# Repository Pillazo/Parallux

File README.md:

The light was designed in Autodesk Fusion 360, but any STEP editor will work. The step file is zipped because the full thing is 250gb-ish

The hardware was designed in KiCad 9.0

The software is arduino IDE, I used ESP32 and Teensy for the microcontrollers

The DMX controller software, which is more sACN anyways, was written in VB.NET

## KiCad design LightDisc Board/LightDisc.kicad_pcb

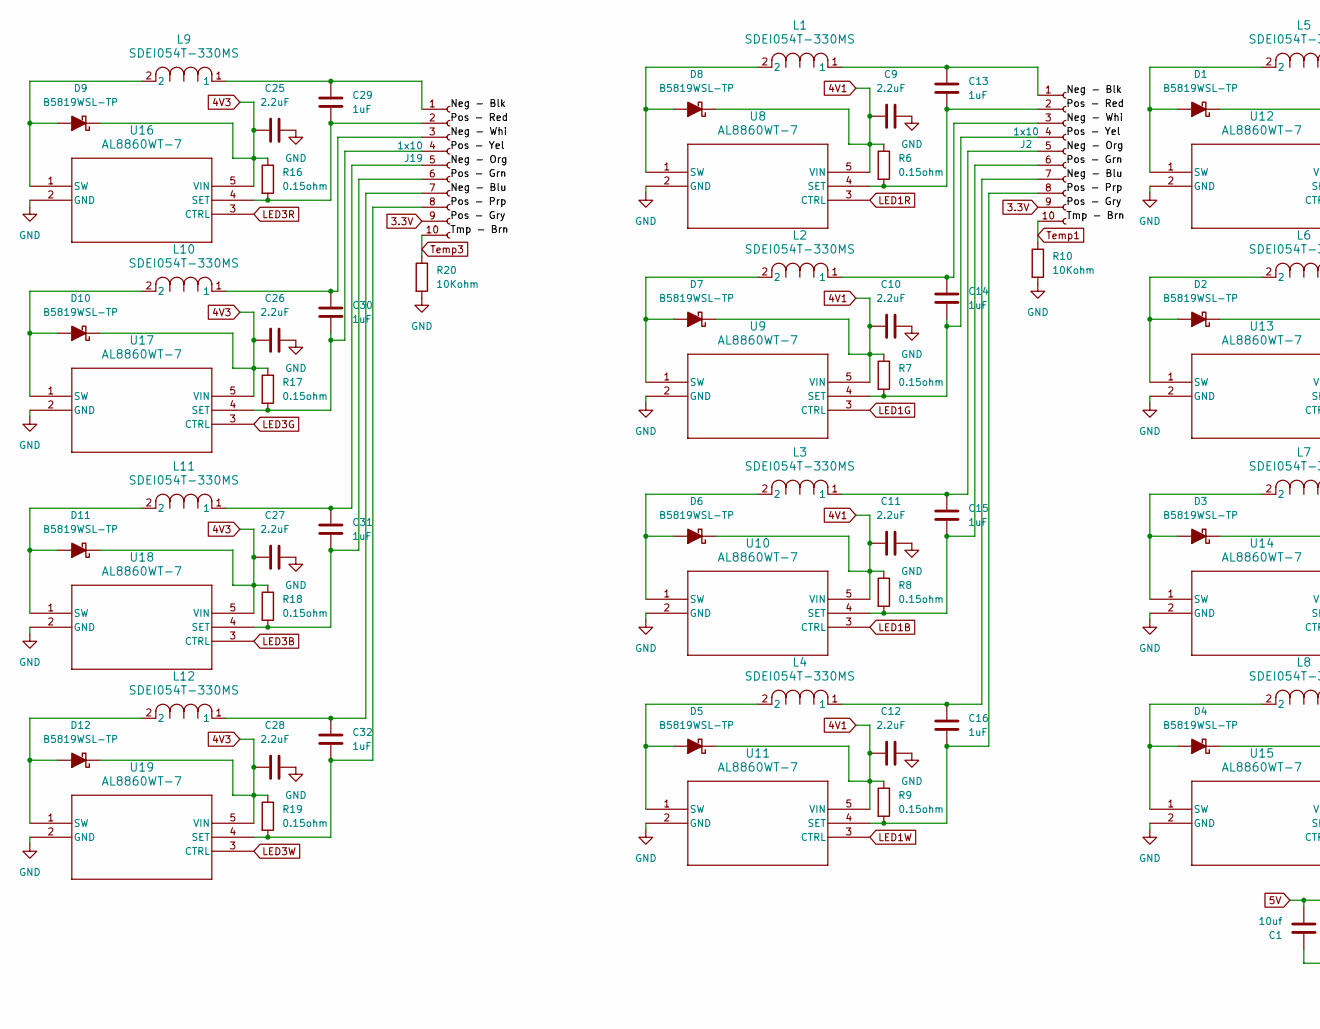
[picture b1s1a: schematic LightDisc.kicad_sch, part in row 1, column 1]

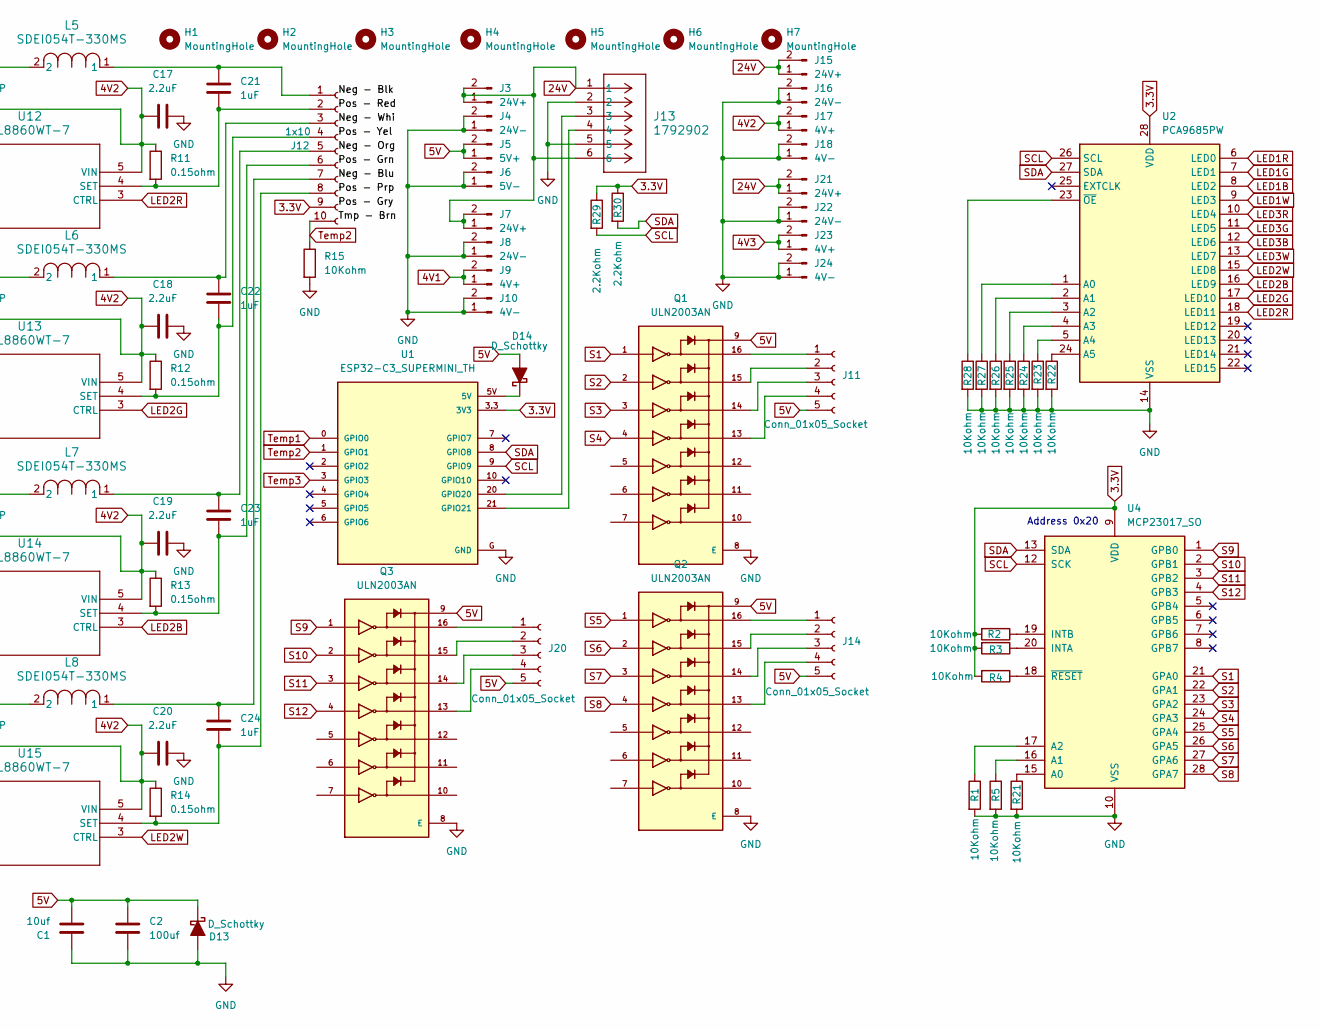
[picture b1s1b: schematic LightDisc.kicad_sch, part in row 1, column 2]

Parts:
C1: 10uf; CP_Radial_D5.0mm_P2.50mm
C2: 100uf; CP_Radial_D5.0mm_P2.50mm
C9, C10, C11, C12, C17, C18, C19, C20, C25, C26, C27, C28: 2.2uF; C_0603_1608Metric
C13, C14, C15, C16, C21, C22, C23, C24, C29, C30, C31, C32: 1uF; C_0603_1608Metric
D1, D2, D3, D4, D5, D6, D7, D8, D9, D10, D11, D12: B5819WSL-TP; D_SOD-323F
D13, D14: D_Schottky; D_SOD-323F
H1, H2, H3, H4, H5, H6, H7: MountingHole; MountingHole_3.2mm_M3
J2, J12, J19: 1x10; JST_EH_B10B-EH-A_1x10_P2.50mm_Vertical
J3, J7, J15, J21: 24V+; PinSocket_1x02_P2.54mm_Vertical
J4, J8, J16, J22: 24V-; PinSocket_1x02_P2.54mm_Vertical
J5: 5V+; PinSocket_1x02_P2.54mm_Vertical
J6: 5V-; PinSocket_1x02_P2.54mm_Vertical
J9, J17, J23: 4V+; PinSocket_1x02_P2.54mm_Vertical
J10, J18, J24: 4V-; PinSocket_1x02_P2.54mm_Vertical
J11, J14, J20: Conn_01x05_Socket; PinSocket_1x05_P2.54mm_Vertical
J13: 1792902; CONN_1792902_PXC
L1, L2, L3, L4, L5, L6, L7, L8, L9, L10, L11, L12: SDEI054T-330MS; IND_SDEI054T-330MS_CYN
Q1, Q2, Q3: ULN2003AN; CERDIP-16_W7.62mm_SideBrazed_LongPads_Socket; PARTREV P
R1, R2, R3, R4, R5, R10, R15, R20, R21, R22, R23, R24, R25, R26, R27, R28: 10Kohm; R_1206_3216Metric
R6, R7, R8, R9, R11, R12, R13, R14, R16, R17, R18, R19: 0.15ohm; R_0805_2012Metric
R29, R30: 2.2Kohm; R_1206_3216Metric
U1: ESP32-C3_SUPERMINI_TH; MODULE_ESP32-C3_SUPERMINI_TH
U2: PCA9685PW; TSSOP-28_4.4x9.7mm_P0.65mm
U4: MCP23017_SO; SOIC-28W_7.5x17.9mm_P1.27mm
U8, U9, U10, U11, U12, U13, U14, U15, U16, U17, U18, U19: AL8860WT-7; TSOT25_WT_DIO

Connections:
3.3V: J2.9, J12.9, J19.9, R2.2, R3.2, R4.2, R29.1, R30.1, U1.3.3 (3V3), U2.28 (VDD), U4.9 (VDD)
4V1: C9.2, C10.2, C11.2, C12.2, D5.1 (K), D6.1 (K), D7.1 (K), D8.1 (K), J9.1, J9.2, R6.1, R7.1, R8.1, R9.1, U8.5 (VIN), U9.5 (VIN), U10.5 (VIN), U11.5 (VIN)
4V2: C17.2, C18.2, C19.2, C20.2, D1.1 (K), D2.1 (K), D3.1 (K), D4.1 (K), J17.1, J17.2, R11.1, R12.1, R13.1, R14.1, U12.5 (VIN), U13.5 (VIN), U14.5 (VIN), U15.5 (VIN)
4V3: C25.2, C26.2, C27.2, C28.2, D9.1 (K), D10.1 (K), D11.1 (K), D12.1 (K), J23.1, J23.2, R16.1, R17.1, R18.1, R19.1, U16.5 (VIN), U17.5 (VIN), U18.5 (VIN), U19.5 (VIN)
5V: C1.2, C2.2, D13.1 (K), D14.2 (A), J5.1, J5.2, J11.5, J14.5, J20.5, Q1.9, Q2.9, Q3.9
24V: J3.1, J3.2, J7.1, J7.2, J13.1, J13.6, J15.1, J15.2, J21.1, J21.2
GND: C1.1, C2.1, C9.1, C10.1, C11.1, C12.1, C17.1, C18.1, C19.1, C20.1, C25.1, C26.1, C27.1, C28.1, D13.2 (A), J4.1, J4.2, J6.1, J6.2, J8.1, J8.2, J10.1, J10.2, J13.2, J13.5, J16.1, J16.2, J18.1, J18.2, J22.1, J22.2, J24.1, J24.2, Q1.8 (E), Q2.8 (E), Q3.8 (E), R1.2, R5.2, R10.2, R15.2, R20.2, R21.2, R22.2, R23.2, R24.2, R25.2, R26.2, R27.2, R28.2, U1.G (GND), U2.14 (VSS), U4.10 (VSS), U8.2 (GND), U9.2 (GND), U10.2 (GND), U11.2 (GND), U12.2 (GND), U13.2 (GND), U14.2 (GND), U15.2 (GND), U16.2 (GND), U17.2 (GND), U18.2 (GND), U19.2 (GND)
LED1B: U2.8 (LED2), U10.3 (CTRL)
LED1G: U2.7 (LED1), U9.3 (CTRL)
LED1R: U2.6 (LED0), U8.3 (CTRL)
LED1W: U2.9 (LED3), U11.3 (CTRL)
LED2B: U2.16 (LED9), U14.3 (CTRL)
LED2G: U2.17 (LED10), U13.3 (CTRL)
LED2R: U2.18 (LED11), U12.3 (CTRL)
LED2W: U2.15 (LED8), U15.3 (CTRL)
LED3B: U2.12 (LED6), U18.3 (CTRL)
LED3G: U2.11 (LED5), U17.3 (CTRL)
LED3R: U2.10 (LED4), U16.3 (CTRL)
LED3W: U2.13 (LED7), U19.3 (CTRL)
unnamed: D1.2 (A), L5.2, U12.1 (SW)
unnamed: D2.2 (A), L6.2, U13.1 (SW)
unnamed: D3.2 (A), L7.2, U14.1 (SW)
unnamed: D4.2 (A), L8.2, U15.1 (SW)
unnamed: D5.2 (A), L4.2, U11.1 (SW)
unnamed: D6.2 (A), L3.2, U10.1 (SW)
unnamed: D7.2 (A), L2.2, U9.1 (SW)
unnamed: D8.2 (A), L1.2, U8.1 (SW)
unnamed: D9.2 (A), L9.2, U16.1 (SW)
unnamed: D10.2 (A), L10.2, U17.1 (SW)
unnamed: D11.2 (A), L11.2, U18.1 (SW)
unnamed: D12.2 (A), L12.2, U19.1 (SW)
unnamed: D14.1 (K), U1.5V
unnamed: C13.1, J2.1, L1.1
unnamed: C13.2, J2.2, R6.2, U8.4 (SET)
unnamed: C14.1, J2.3, L2.1
unnamed: C14.2, J2.4, R7.2, U9.4 (SET)
unnamed: C15.1, J2.5, L3.1
unnamed: C15.2, J2.6, R8.2, U10.4 (SET)
unnamed: C16.1, J2.7, L4.1
unnamed: C16.2, J2.8, R9.2, U11.4 (SET)
unnamed: J11.1, Q1.16
unnamed: J11.2, Q1.15
unnamed: J11.3, Q1.14
unnamed: J11.4, Q1.13
unnamed: C21.1, J12.1, L5.1
unnamed: C21.2, J12.2, R11.2, U12.4 (SET)
unnamed: C22.1, J12.3, L6.1
unnamed: C22.2, J12.4, R12.2, U13.4 (SET)
unnamed: C23.1, J12.5, L7.1
unnamed: C23.2, J12.6, R13.2, U14.4 (SET)
unnamed: C24.1, J12.7, L8.1
unnamed: C24.2, J12.8, R14.2, U15.4 (SET)
unnamed: J14.1, Q2.16
unnamed: J14.2, Q2.15
unnamed: J14.3, Q2.14
unnamed: J14.4, Q2.13
unnamed: C29.1, J19.1, L9.1
unnamed: C29.2, J19.2, R16.2, U16.4 (SET)
unnamed: C30.1, J19.3, L10.1
unnamed: C30.2, J19.4, R17.2, U17.4 (SET)
unnamed: C31.1, J19.5, L11.1
unnamed: C31.2, J19.6, R18.2, U18.4 (SET)
unnamed: C32.1, J19.7, L12.1
unnamed: C32.2, J19.8, R19.2, U19.4 (SET)
unnamed: J20.1, Q3.16
unnamed: J20.2, Q3.15
unnamed: J20.3, Q3.14
unnamed: J20.4, Q3.13
unnamed: J13.3, U1.20 (GPIO20)
unnamed: J13.4, U1.21 (GPIO21)
unnamed: R27.1, U2.1 (A0)
unnamed: R26.1, U2.2 (A1)
unnamed: R25.1, U2.3 (A2)
unnamed: R24.1, U2.4 (A3)
unnamed: R23.1, U2.5 (A4)
unnamed: R22.1, U2.24 (A5)
unnamed: R28.1, U2.23 (~OE)
unnamed: R21.1, U4.15 (A0)
unnamed: R5.1, U4.16 (A1)
unnamed: R1.1, U4.17 (A2)
unnamed: R3.1, U4.20 (INTA)
unnamed: R2.1, U4.19 (INTB)
unnamed: R4.1, U4.18 (~RESET)
S1: Q1.1, U4.21 (GPA0)
S2: Q1.2, U4.22 (GPA1)
S3: Q1.3, U4.23 (GPA2)
S4: Q1.4, U4.24 (GPA3)
S5: Q2.1, U4.25 (GPA4)
S6: Q2.2, U4.26 (GPA5)
S7: Q2.3, U4.27 (GPA6)
S8: Q2.4, U4.28 (GPA7)
S9: Q3.1, U4.1 (GPB0)
S10: Q3.2, U4.2 (GPB1)
S11: Q3.3, U4.3 (GPB2)
S12: Q3.4, U4.4 (GPB3)
SCL: R29.2, U1.9 (GPIO9), U2.26 (SCL), U4.12 (SCK)
SDA: R30.2, U1.8 (GPIO8), U2.27 (SDA), U4.13 (SDA)
Temp1: J2.10, R10.1, U1.0 (GPIO0)
Temp2: J12.10, R15.1, U1.1 (GPIO1)
Temp3: J19.10, R20.1, U1.2 (GPIO2), U1.3 (GPIO3)

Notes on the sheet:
Address 0x20

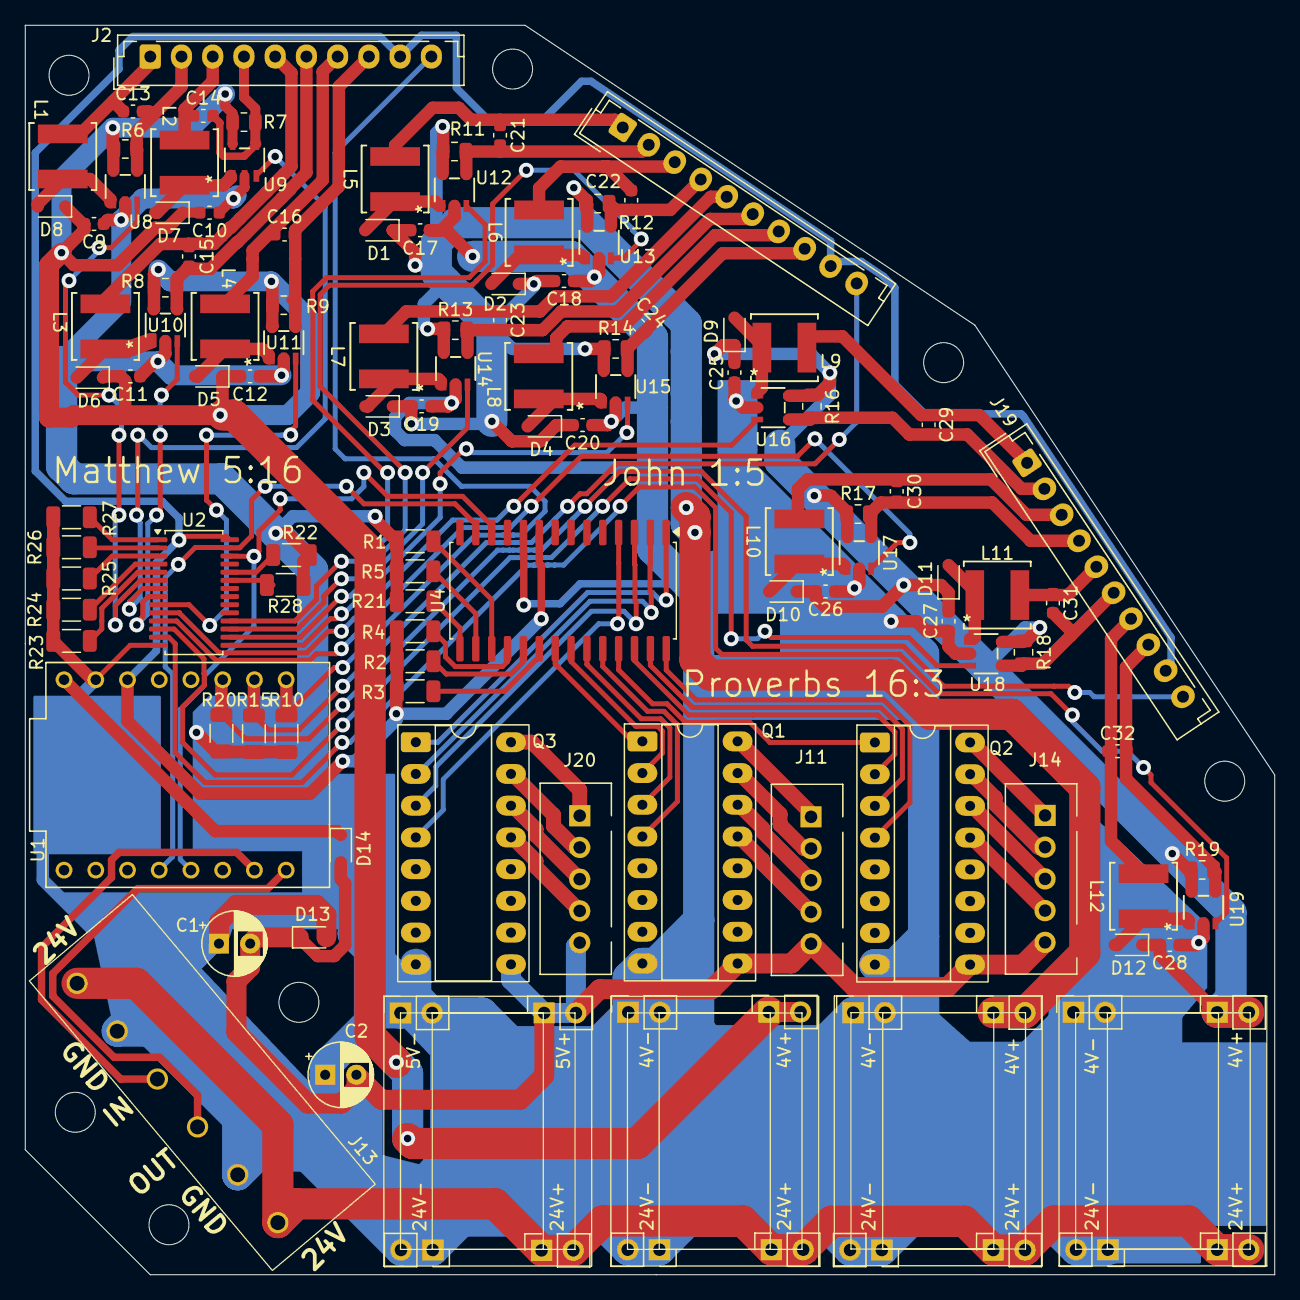
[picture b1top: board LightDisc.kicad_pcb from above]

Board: 2 copper layers, 100.0 x 100.0 mm, 128 parts (0 on the bottom side), 100 nets.

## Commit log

2026-02-09 Main Dump
    All the OG files of version 1
